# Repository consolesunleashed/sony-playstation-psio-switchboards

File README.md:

# Sony PlayStation PSIO Switchboards

My set of PSIO switchboard designed to make installs cleaner than the supplied switchboard.

## Why?

At a time when I was doing weekly PSIO installs I designed some new switchboards to make installs cleaner in all revisions. Somewhat redundant now SIO-XS exists. I am including them here as a curiosity.

## Version History

- PSIO Switchboard PU-8 v1 - 23/11/2020
- PSIO Switchboard PU-18 v1 - 23/11/2020
- PSIO Switchboard PU-20 v1 - 23/11/2020
- PSIO Switchboard PU-22 v1 - 23/11/2020

## Donate

Working on designs to release for free can be both time consuming and expensive. If you like what I do, a small donation will go a long way in helping me continue to serve the modding community as best as I can, with many more free and original guides, designs, and ideas to come.

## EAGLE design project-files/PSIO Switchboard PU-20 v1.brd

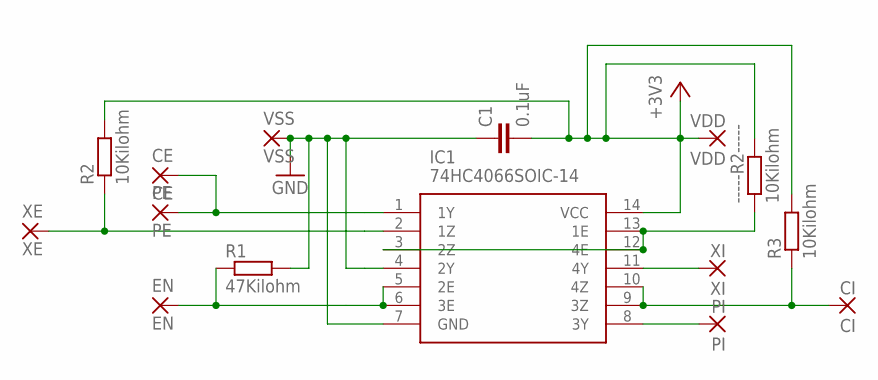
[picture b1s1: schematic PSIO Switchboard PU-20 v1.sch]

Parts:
-----R2-----: 10Kilohm; R0805
C1: 0.1uF; C0805
CE: CE; CIRCLE-2X2
CI: CI; CIRCLE-2X2
EN: EN; CIRCLE-2X2
IC1: 74HC4066SOIC-14; SOIC-14
PE: PE; CIRCLE-2X2
PI: PI; CIRCLE-2X2
R1: 47Kilohm; R0805
R2, R3: 10Kilohm; R0805
VDD: VDD; CIRCLE-2X2
VSS: VSS; CIRCLE-2X2
XE: XE; CIRCLE-2X2
XI: XI; CIRCLE-2X2

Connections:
+3V3: -----R2-----.2, C1.2, IC1.14 (VCC), R2.2, R3.2, VDD.1
CI: CI.1, IC1.9 (3Z), IC1.10 (4Z), R3.1
EN: EN.1, IC1.5 (2E), IC1.6 (3E), R1.1
GND: C1.1, IC1.4 (2Y), IC1.7 (GND), R1.2, VSS.1
unnamed: -----R2-----.1, IC1.3 (2Z), IC1.12 (4E), IC1.13 (1E)
PE-CE: CE.1, IC1.1 (1Y), PE.1
PI: IC1.8 (3Y), PI.1
XE: IC1.2 (1Z), R2.1, XE.1
XI: IC1.11 (4Y), XI.1

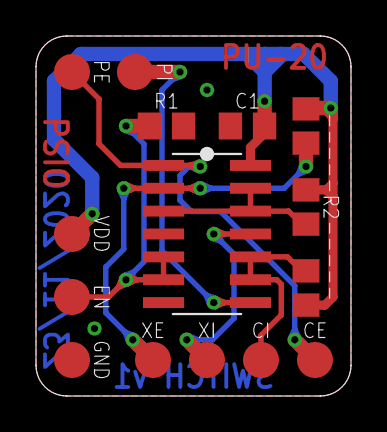
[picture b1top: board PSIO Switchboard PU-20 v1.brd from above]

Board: 2 copper layers, 17.5 x 20.0 mm, 15 parts (0 on the bottom side), 9 nets.

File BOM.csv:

Designation,Part,MPN,Value,Case/Size,Amount
,Quad SPST Analog Switch,74HC4066,,SOIC-14,1
C1,Capacitor,,0.1uF / 25V,0803,1
R2,Resistor,,10Kilohm,0803,3
R1,Resistor,,47Kilohm,0803,1
